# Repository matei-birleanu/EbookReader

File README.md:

# 📘 System Overview

This project brings together multiple hardware components to form a compact, smart, and efficient embedded system. It supports wireless communication, environmental monitoring, timekeeping, data storage, battery management, and user interaction via a low-power display.

---
## Schema Bloc

## 🔧 Components

### 🔲 **ESP32-C6-WROOM-1-N8**
- Acts as the main controller managing all tasks and data flow.
- Supports multiple wireless protocols: Wi-Fi, Bluetooth, Zigbee, and Thread.

### ⏱️ **RTC Module - DS3231SN**
- Ensures precise timekeeping.
- Communicates with the microcontroller via the I2C bus.

### 💾 **Flash Memory - W25Q512JVEIQ**
- High-speed storage accessed through the SPI interface.
- Used for firmware storage and persistent data.

### 🔋 **Battery Charging IC - MCP73831**
- Manages the charging process of a Li-Ion battery through the USB Type-C port.
- GPIO pins are used to monitor charging status and control power logic.

### ⚡ **Fuel Gauge - MAX17048G+T10**
- Estimates the battery's state of charge.
- Interfaces with the microcontroller over I2C.

### 🌡️ **Environmental Sensor - BME680**
- Measures temperature, humidity, atmospheric pressure, and gas levels.
- I2C-based communication.

### 🖼️ **ePaper Display**
- Displays system information to the user.
- Controlled via the SPI protocol for fast and efficient updates.

### 💽 **SD Card Slot (J4)**
- Enables external storage expansion.
- Useful for data logging or firmware upgrades.
- Communicates using the SPI interface.

### 🔌 **USB Type-C Port (J2)**
- Primary power supply for the device.
- Includes USB data lines (D+ and D−) for host communication.

---

## 📍 ESP32-C6 Pin Mapping

| ESP32-C6 Pin | Description |
|--------------|-------------|
| 3V3          | 3.3V output to power the charging circuit |
| EN           | Reset button |
| IO0          | Alert/timing signal from RTC |
| IO1          | Clock reference from RTC |
| IO2          | SPI - MISO (Master In Slave Out) |
| IO3          | ePaper display busy status |
| IO4          | SD card communication |
| IO5          | ePaper D/C (Data/Command select) |
| IO6          | SPI Clock (SCK) |
| IO7          | SPI - MOSI (Master Out Slave In) |
| IO8          | (Reserved/Unused) |
| IO9          | Boot button |
| IO10         | Chip Select for ePaper |
| IO11         | Chip Select for Flash memory |
| IO12         | USB D+ |
| IO13         | USB D− |
| IO15         | Mode switch button |
| TXD0 (IO16)  | UART TX for debugging |
| RXD0 (IO17)  | UART RX for debugging |
| IO18         | RTC reset |
| IO19         | I2C power line |
| IO20         | Power supply for the display |
| IO21         | I2C SDA (data line) |
| IO22         | I2C SCL (clock line) |
| IO23         | Display reset |
| GND          | Ground |

---

## BOM (Bill of Materials)

**Note**: TP-urile au fost construite de mine.

| Nr. piesa | Nume piesa       | Site                                                                                                                                           | Datasheet                                                                                                                                                    |
|-----------|------------------|------------------------------------------------------------------------------------------------------------------------------------------------|--------------------------------------------------------------------------------------------------------------------------------------------------------------|
| 1         | BOOT_BUTON       | [Link](https://www.snapeda.com/parts/EVQP7L01P/Panasonic%20Electronic%20Components/view-part/?welcome=home)                                   | [Datasheet](https://www.snapeda.com/parts/EVQP7L01P/Panasonic/datasheet/)                                                                                   |
| 2         | C1               | [Link](https://componentsearchengine.com/part-view/CC0402MRX5R5BB106/YAGEO)                                                                    | [Datasheet](https://componentsearchengine.com/Datasheets/2/CC0402MRX5R5BB106.pdf)                                                                           |
| 3         | C1_BAT           | [Link](https://componentsearchengine.com/part-view/CC0402MRX5R5BB106/YAGEO)                                                                    | [Datasheet](https://componentsearchengine.com/Datasheets/2/CC0402MRX5R5BB106.pdf)                                                                           |
| 4         | C1_BAT2          | [Link](https://componentsearchengine.com/part-view/CC0402MRX5R5BB106/YAGEO)                                                                    | [Datasheet](https://componentsearchengine.com/Datasheets/2/CC0402MRX5R5BB106.pdf)                                                                           |
| 5         | C2               | [Link](https://componentsearchengine.com/part-view/CC0402MRX5R5BB106/YAGEO)                                                                    | [Datasheet](https://componentsearchengine.com/Datasheets/2/CC0402MRX5R5BB106.pdf)                                                                           |
| 6         | C2_BAT           | [Link](https://componentsearchengine.com/part-view/CC0402MRX5R5BB106/YAGEO)                                                                    | [Datasheet](https://componentsearchengine.com/Datasheets/2/CC0402MRX5R5BB106.pdf)                                                                           |
| 7         | C3               | [Link](https://componentsearchengine.com/part-view/CC0402MRX5R5BB106/YAGEO)                                                                    | [Datasheet](https://componentsearchengine.com/Datasheets/2/CC0402MRX5R5BB106.pdf)                                                                           |
| 8         | C4               | [Link](https://componentsearchengine.com/part-view/CC0402MRX5R5BB106/YAGEO)                                                                    | [Datasheet](https://componentsearchengine.com/Datasheets/2/CC0402MRX5R5BB106.pdf)                                                                           |
| 9         | C4_USB           | [Link](https://componentsearchengine.com/part-view/CC0402MRX5R5BB106/YAGEO)                                                                    | [Datasheet](https://componentsearchengine.com/Datasheets/2/CC0402MRX5R5BB106.pdf)                                                                           |
| 10        | C5               | [Link](https://componentsearchengine.com/part-view/CC0402MRX5R5BB106/YAGEO)                                                                    | [Datasheet](https://componentsearchengine.com/Datasheets/2/CC0402MRX5R5BB106.pdf)                                                                           |
| 11        | C5_USB           | [Link](https://componentsearchengine.com/part-view/CC0402MRX5R5BB106/YAGEO)                                                                    | [Datasheet](https://componentsearchengine.com/Datasheets/2/CC0402MRX5R5BB106.pdf)                                                                           |
| 12        | C6               | [Link](https://componentsearchengine.com/part-view/CC0402MRX5R5BB106/YAGEO)                                                                    | [Datasheet](https://componentsearchengine.com/Datasheets/2/CC0402MRX5R5BB106.pdf)                                                                           |
| 13        | C7               | [Link](https://componentsearchengine.com/part-view/CC0402MRX5R5BB106/YAGEO)                                                                    | [Datasheet](https://componentsearchengine.com/Datasheets/2/CC0402MRX5R5BB106.pdf)                                                                           |
| 14        | C8               | [Link](https://componentsearchengine.com/part-view/CC0402MRX5R5BB106/YAGEO)                                                                    | [Datasheet](https://componentsearchengine.com/Datasheets/2/CC0402MRX5R5BB106.pdf)                                                                           |
| 15        | C9               | [Link](https://componentsearchengine.com/part-view/CC0402MRX5R5BB106/YAGEO)                                                                    | [Datasheet](https://componentsearchengine.com/Datasheets/2/CC0402MRX5R5BB106.pdf)                                                                           |
| 16        | C10              | [Link](https://componentsearchengine.com/part-view/CC0402MRX5R5BB106/YAGEO)                                                                    | [Datasheet](https://componentsearchengine.com/Datasheets/2/CC0402MRX5R5BB106.pdf)                                                                           |
| 17        | C10_SUPERCAR     | [Link](https://industry.panasonic.com/global/en/products/control/switch/light-touch/number/evqpuj02k)                                          | [Datasheet](https://industry.panasonic.com/global/en/downloads?tab=catalog&small_g_cd=203&part_no=EVQPUJ02K)                                                |
| 18        | CHANGE_BUTTON    | [Link](https://www.snapeda.com/parts/EVQP7L01P/Panasonic%20Electronic%20Components/view-part/?welcome=home)                                   | [Datasheet](https://www.snapeda.com/parts/EVQP7L01P/Panasonic/datasheet/)                                                                                   |
| 19        | C_DELAY          | [Link](https://componentsearchengine.com/part-view/CC0402MRX5R5BB106/YAGEO)                                                                    | [Datasheet](https://componentsearchengine.com/Datasheets/2/CC0402MRX5R5BB106.pdf)                                                                           |
| 20        | D1               | [Link](https://www.snapeda.com/parts/USBLC6-2SC6Y/STMicroelectronics/view-part/?ref=eda)                                                      | [Datasheet](https://www.snapeda.com/parts/USBLC6-2SC6Y/STMicroelectronics/view-part/?ref=eda)                                                               |
| 21        | D2               | [Link](https://ro.mouser.com/ProductDetail/KYOCERA-AVX/SD0805S020S1R0?qs=jCA%252BPfw4LHbpkAoSnwrdjw%3D%3D)                                      | [Datasheet](https://ro.mouser.com/datasheet/2/40/schottky-3165252.pdf)                                                                                      |
| 22        | D3               | [Link](https://ro.mouser.com/ProductDetail/KYOCERA-AVX/SD0805S020S1R0?qs=jCA%252BPfw4LHbpkAoSnwrdjw%3D%3D)                                      | [Datasheet](https://ro.mouser.com/datasheet/2/40/schottky-3165252.pdf)                                                                                      |
| 23        | D4               | [Link](https://ro.mouser.com/ProductDetail/KYOCERA-AVX/SD0805S020S1R0?qs=jCA%252BPfw4LHbpkAoSnwrdjw%3D%3D)                                      | [Datasheet](https://ro.mouser.com/datasheet/2/40/schottky-3165252.pdf)                                                                                      |
| 24        | D5               | [Link](https://ro.mouser.com/ProductDetail/KYOCERA-AVX/SD0805S020S1R0?qs=jCA%252BPfw4LHbpkAoSnwrdjw%3D%3D)                                      | [Datasheet](https://ro.mouser.com/datasheet/2/40/schottky-3165252.pdf)                                                                                      |
| 25        | D6               | [Link](https://www.snapeda.com/parts/PGB1010603MR/Littelfuse/view-part/?ref=eda)                                                              | [Datasheet](https://www.snapeda.com/parts/PGB1010603MR/Littelfuse%20Inc./datasheet/)                                                                        |
| 26        | D7               | [Link](https://ro.mouser.com/ProductDetail/KYOCERA-AVX/SD0805S020S1R0?qs=jCA%252BPfw4LHbpkAoSnwrdjw%3D%3D)                                      | [Datasheet](https://ro.mouser.com/datasheet/2/40/schottky-3165252.pdf)                                                                                      |
| 27        | D8               | [Link](https://www.snapeda.com/parts/PGB1010603MR/Littelfuse/view-part/?ref=eda)                                                              | [Datasheet](https://www.snapeda.com/parts/PGB1010603MR/Littelfuse%20Inc./datasheet/)                                                                        |
| 28        | D9               | [Link](https://www.snapeda.com/parts/PGB1010603MR/Littelfuse/view-part/?ref=eda)                                                              | [Datasheet](https://www.snapeda.com/parts/PGB1010603MR/Littelfuse%20Inc./datasheet/)                                                                        |
| 29        | D10              | [Link](https://www.snapeda.com/parts/PGB1010603MR/Littelfuse/view-part/?ref=eda)                                                              | [Datasheet](https://www.snapeda.com/parts/PGB1010603MR/Littelfuse%20Inc./datasheet/)                                                                        |
| 30        | D11              | [Link](https://www.snapeda.com/parts/PGB1010603MR/Littelfuse/view-part/?ref=eda)                                                              | [Datasheet](https://www.snapeda.com/parts/PGB1010603MR/Littelfuse%20Inc./datasheet/)                                                                        |
| 31        | D12              | [Link](https://www.snapeda.com/parts/PGB1010603MR/Littelfuse/view-part/?ref=eda)                                                              | [Datasheet](https://www.snapeda.com/parts/PGB1010603MR/Littelfuse%20Inc./datasheet/)                                                                        |
| 32        | EPD_C1           | [Link](https://componentsearchengine.com/part-view/CC0402MRX5R5BB106/YAGEO)                                                                    | [Datasheet](https://componentsearchengine.com/Datasheets/2/CC0402MRX5R5BB106.pdf)                                                                           |
| 33        | EPD_C2           | [Link](https://componentsearchengine.com/part-view/CC0402MRX5R5BB106/YAGEO)                                                                    | [Datasheet](https://componentsearchengine.com/Datasheets/2/CC0402MRX5R5BB106.pdf)                                                                           |
| 34        | EPD_C5           | [Link](https://componentsearchengine.com/part-view/CC0402MRX5R5BB106/YAGEO)                                                                    | [Datasheet](https://componentsearchengine.com/Datasheets/2/CC0402MRX5R5BB106.pdf)                                                                           |
| 35        | EPD_C6           | [Link](https://componentsearchengine.com/part-view/CC0402MRX5R5BB106/YAGEO)                                                                    | [Datasheet](https://componentsearchengine.com/Datasheets/2/CC0402MRX5R5BB106.pdf)                                                                           |
| 36        | EPD_C7           | [Link](https://componentsearchengine.com/part-view/CC0402MRX5R5BB106/YAGEO)                                                                    | [Datasheet](https://componentsearchengine.com/Datasheets/2/CC0402MRX5R5BB106.pdf)                                                                           |
| 37        | EPD_C8           | [Link](https://componentsearchengine.com/part-view/CC0402MRX5R5BB106/YAGEO)                                                                    | [Datasheet](https://componentsearchengine.com/Datasheets/2/CC0402MRX5R5BB106.pdf)                                                                           |
| 38        | EPD_C9           | [Link](https://componentsearchengine.com/part-view/CC0402MRX5R5BB106/YAGEO)                                                                    | [Datasheet](https://componentsearchengine.com/Datasheets/2/CC0402MRX5R5BB106.pdf)                                                                           |
| 39        | EPD_C10          | [Link](https://componentsearchengine.com/part-view/CC0402MRX5R5BB106/YAGEO)                                                                    | [Datasheet](https://componentsearchengine.com/Datasheets/2/CC0402MRX5R5BB106.pdf)                                                                           |
| 40        | EPD_C11          | [Link](https://componentsearchengine.com/part-view/CC0402MRX5R5BB106/YAGEO)                                                                    | [Datasheet](https://componentsearchengine.com/Datasheets/2/CC0402MRX5R5BB106.pdf)                                                                           |
| 41        | EPD_C12          | [Link](https://componentsearchengine.com/part-view/CC0402MRX5R5BB106/YAGEO)                                                                    | [Datasheet](https://componentsearchengine.com/Datasheets/2/CC0402MRX5R5BB106.pdf)                                                                           |
| 42        | IC1              | [Link](https://componentsearchengine.com/part-view/BD5229G-TR/ROHM%20Semiconductor)                                                            | [Datasheet](https://datasheet.datasheetarchive.com/originals/distributors/Datasheets_SAMA/f2b9741ef86007909f138d561a359946.pdf)                             |
| 43        | IC4              | [Link](https://componentsearchengine.com/part-view/XC6220A331MR-G/Torex)                                                                       | [Datasheet](https://product.torexsemi.com/system/files/series/xc6220.pdf)                                                                                   |
| 44        | J1               | [Link](https://componentsearchengine.com/part-view/FH34SRJ-24S-0.5SH%2899%29/Hirose)                                                           | [Datasheet](https://www.hirose.com/en/product/document?clcode=CL0580-1255-6-99&productname=FH34SRJ-24S-0.5SH%2899%29&series=FH34SRJ&documenttype=2DDrawing&lang=en&documentid=0000990903) |
| 45        | J2               | [Link](https://componentsearchengine.com/part-view/USB4110-GF-A/GCT%20(GLOBAL%20CONNECTOR%20TECHNOLOGY))                                       | [Datasheet](https://gct.co/files/drawings/usb4110.pdf)                                                                                                      |
| 46        | J3               | [Link](https://www.snapeda.com/parts/PRT-14417/SparkFun/view-part/)                                                                            | [Datasheet](https://www.snapeda.com/parts/PRT-14417/SparkFun%20Electronics/datasheet/)                                                                       |
| 47        | J4               | [Link](https://www.snapeda.com/parts/112A-TAAR-R03/Attend/view-part/)                                                                          | [Datasheet](https://www.snapeda.com/parts/112A-TAAR-R03/Attend/datasheet/)                                                                                  |
| 48        | MCP73831         | [Link](https://ro.mouser.com/ProductDetail/Microchip-Technology/MCP73831T-2ACI-OT?qs=yUQqVecv4qvbBQBGbHx0Mw%3D%3D&utm_id=20109199409&utm_source=google&utm_medium=cpc&utm_marketing_tactic=emeacorp&gad_source=1&gbraid=0AAAAADn_wf0-USzm1eg1ywGvQg_qMgG3H) | [Datasheet](https://ro.mouser.com/datasheet/2/268/MCP73831_Family_Data_Sheet_DS20001984H-3441711.pdf)                                                       |
| 49        | L1               | [Link](https://ro.mouser.com/ProductDetail/Wurth-Elektronik/744043680?qs=PGXP4M47uW6VkZq%252BkzjrHA%3D%3D)                                       | [Datasheet](https://www.we-online.com/components/products/datasheet/744043680.pdf)                                                                          |
| 50        | PFMF.050.1       | [Link](https://ro.mouser.com/ProductDetail/EPCOS-TDK/B72520T0350K062?qs=dEfas%2FXlABIszF52uu7vrg%3D%3D)                                         | [Datasheet](https://www.tdk-electronics.tdk.com/inf/75/db/CTVS_14/Surge_protection_series.pdf)                                                              |
| 51        | Q1               | [Link](https://componentsearchengine.com/part-view/DMG2305UX-7/Diodes%20Incorporated)                                                          | [Datasheet](https://www.diodes.com//assets/Datasheets/DMG2305UX.pdf)                                                                                        |
| 52        | Q2               | [Link](https://componentsearchengine.com/part-view/DMG2305UX-7/Diodes%20Incorporated)                                                          | [Datasheet](https://www.diodes.com//assets/Datasheets/DMG2305UX.pdf)                                                                                        |
| 53        | Q3               | [Link](https://componentsearchengine.com/part-view/SI1308EDL-T1-GE3/Vishay)                                                                     | [Datasheet](https://componentsearchengine.com/part-view/SI1308EDL-T1-GE3/Vishay)                                                                             |
| 54        | R1               | [Link](https://componentsearchengine.com/part-view/R0402%201%25%20100%20K%20%28RC0402FR-07100KL%29/YAGEO)                                       | [Datasheet](https://www.yageo.com/upload/media/product/products/datasheet/rchip/PYu-RC_Group_51_RoHS_L_12.pdf)                                              |
| 55        | R1_PINH          | [Link](https://componentsearchengine.com/part-view/R0402%201%25%20100%20K%20%28RC0402FR-07100KL%29/YAGEO)                                       | [Datasheet](https://www.yageo.com/upload/media/product/products/datasheet/rchip/PYu-RC_Group_51_RoHS_L_12.pdf)                                              |
| 56        | R1_PINH1         | [Link](https://componentsearchengine.com/part-view/R0402%201%25%20100%20K%20%28RC0402FR-07100KL%29/YAGEO)                                       | [Datasheet](https://www.yageo.com/upload/media/product/products/datasheet/rchip/PYu-RC_Group_51_RoHS_L_12.pdf)                                              |
| 57        | R1_BAT           | [Link](https://componentsearchengine.com/part-view/R0402%201%25%20100%20K%20%28RC0402FR-07100KL%29/YAGEO)                                       | [Datasheet](https://www.yageo.com/upload/media/product/products/datasheet/rchip/PYu-RC_Group_51_RoHS_L_12.pdf)                                              |
| 58        | R1_PWRUSB        | [Link](https://componentsearchengine.com/part-view/R0402%201%25%20100%20K%20%28RC0402FR-07100KL%29/YAGEO)                                       | [Datasheet](https://www.yageo.com/upload/media/product/products/datasheet/rchip/PYu-RC_Group_51_RoHS_L_12.pdf)                                              |
| 59        | R2               | [Link](https://componentsearchengine.com/part-view/R0402%201%25%20100%20K%20%28RC0402FR-07100KL%29/YAGEO)                                       | [Datasheet](https://www.yageo.com/upload/media/product/products/datasheet/rchip/PYu-RC_Group_51_RoHS_L_12.pdf)                                              |
| 60        | R2_PINH          | [Link](https://componentsearchengine.com/part-view/R0402%201%25%20100%20K%20%28RC0402FR-07100KL%29/YAGEO)                                       | [Datasheet](https://www.yageo.com/upload/media/product/products/datasheet/rchip/PYu-RC_Group_51_RoHS_L_12.pdf)                                              |
| 61        | R2-PINH1         | [Link](https://componentsearchengine.com/part-view/R0402%201%25%20100%20K%20%28RC0402FR-07100KL%29/YAGEO)                                       | [Datasheet](https://www.yageo.com/upload/media/product/products/datasheet/rchip/PYu-RC_Group_51_RoHS_L_12.pdf)                                              |
| 62        | R2               | [Link](https://componentsearchengine.com/part-view/R0402%201%25%20100%20K%20%28RC0402FR-07100KL%29/YAGEO)                                       | [Datasheet](https://www.yageo.com/upload/media/product/products/datasheet/rchip/PYu-RC_Group_51_RoHS_L_12.pdf)                                              |
| 63        | R2-PINH          | [Link](https://componentsearchengine.com/part-view/R0402%201%25%20100%20K%20%28RC0402FR-07100KL%29/YAGEO)                                       | [Datasheet](https://www.yageo.com/upload/media/product/products/datasheet/rchip/PYu-RC_Group_51_RoHS_L_12.pdf)                                              |
| 64        | R2-PINH1         | [Link](https://componentsearchengine.com/part-view/R0402%201%25%20100%20K%20%28RC0402FR-07100KL%29/YAGEO)                                       | [Datasheet](https://www.yageo.com/upload/media/product/products/datasheet/rchip/PYu-RC_Group_51_RoHS_L_12.pdf)                                              |
| 65        | R2_USB           | [Link](https://componentsearchengine.com/part-view/R0402%201%25%20100%20K%20%28RC0402FR-07100KL%29/YAGEO)                                       | [Datasheet](https://www.yageo.com/upload/media/product/products/datasheet/rchip/PYu-RC_Group_51_RoHS_L_12.pdf)                                              |
| 66        | R2_USB           | [Link](https://componentsearchengine.com/part-view/R0402%201%25%20100%20K%20%28RC0402FR-07100KL%29/YAGEO)                                       | [Datasheet](https://www.yageo.com/upload/media/product/products/datasheet/rchip/PYu-RC_Group_51_RoHS_L_12.pdf)                                              |
| 67        | R2_USB1          | [Link](https://componentsearchengine.com/part-view/R0402%201%25%20100%20K%20%28RC0402FR-07100KL%29/YAGEO)                                       | [Datasheet](https://www.yageo.com/upload/media/product/products/datasheet/rchip/PYu-RC_Group_51_RoHS_L_12.pdf)                                              |
| 68        | R3               | [Link](https://componentsearchengine.com/part-view/R0402%201%25%20100%20K%20%28RC0402FR-07100KL%29/YAGEO)                                       | [Datasheet](https://www.yageo.com/upload/media/product/products/datasheet/rchip/PYu-RC_Group_51_RoHS_L_12.pdf)                                              |
| 69        | R4               | [Link](https://componentsearchengine.com/part-view/R0402%201%25%20100%20K%20%28RC0402FR-07100KL%29/YAGEO)                                       | [Datasheet](https://www.yageo.com/upload/media/product/products/datasheet/rchip/PYu-RC_Group_51_RoHS_L_12.pdf)                                              |
| 70        | R5               | [Link](https://componentsearchengine.com/part-view/R0402%201%25%20100%20K%20%28RC0402FR-07100KL%29/YAGEO)                                       | [Datasheet](https://www.yageo.com/upload/media/product/products/datasheet/rchip/PYu-RC_Group_51_RoHS_L_12.pdf)                                              |
| 71        | R6               | [Link](https://componentsearchengine.com/part-view/R0402%201%25%20100%20K%20%28RC0402FR-07100KL%29/YAGEO)                                       | [Datasheet](https://www.yageo.com/upload/media/product/products/datasheet/rchip/PYu-RC_Group_51_RoHS_L_12.pdf)                                              |
| 72        | R7               | [Link](https://componentsearchengine.com/part-view/R0402%201%25%20100%20K%20%28RC0402FR-07100KL%29/YAGEO)                                       | [Datasheet](https://www.yageo.com/upload/media/product/products/datasheet/rchip/PYu-RC_Group_51_RoHS_L_12.pdf)                                              |
| 73        | R8               | [Link](https://componentsearchengine.com/part-view/R0402%201%25%20100%20K%20%28RC0402FR-07100KL%29/YAGEO)                                       | [Datasheet](https://www.yageo.com/upload/media/product/products/datasheet/rchip/PYu-RC_Group_51_RoHS_L_12.pdf)                                              |
| 74        | R9               | [Link](https://componentsearchengine.com/part-view/R0402%201%25%20100%20K%20%28RC0402FR-07100KL%29/YAGEO)                                       | [Datasheet](https://www.yageo.com/upload/media/product/products/datasheet/rchip/PYu-RC_Group_51_RoHS_L_12.pdf)                                              |
| 75        | R10              | [Link](https://componentsearchengine.com/part-view/R0402%201%25%20100%20K%20%28RC0402FR-07100KL%29/YAGEO)                                       | [Datasheet](https://www.yageo.com/upload/media/product/products/datasheet/rchip/PYu-RC_Group_51_RoHS_L_12.pdf)                                              |
| 76        | RESET_BUTTON     | [Link](https://www.snapeda.com/parts/EVQP7L01P/Panasonic%20Electronic%20Components/view-part/?welcome=home)                                   | [Datasheet](https://www.snapeda.com/parts/EVQP7L01P/Panasonic/datasheet/)                                                                                   |
| 77        | R_BOOT           | [Link](https://componentsearchengine.com/part-view/R0402%201%25%20100%20K%20%28RC0402FR-07100KL%29/YAGEO)                                       | [Datasheet](https://www.yageo.com/upload/media/product/products/datasheet/rchip/PYu-RC_Group_51_RoHS_L_12.pdf)                                              |
| 78        | R_CAPACITOR      | [Link](https://componentsearchengine.com/part-view/R0402%201%25%20100%20K%20%28RC0402FR-07100KL%29/YAGEO)                                       | [Datasheet](https://www.yageo.com/upload/media/product/products/datasheet/rchip/PYu-RC_Group_51_RoHS_L_12.pdf)                                              |
| 79        | R_CHANGE         | [Link](https://componentsearchengine.com/part-view/R0402%201%25%20100%20K%20%28RC0402FR-07100KL%29/YAGEO)                                       | [Datasheet](https://www.yageo.com/upload/media/product/products/datasheet/rchip/PYu-RC_Group_51_RoHS_L_12.pdf)                                              |
| 80        | R_CL1            | [Link](https://componentsearchengine.com/part-view/R0402%201%25%20100%20K%20%28RC0402FR-07100KL%29/YAGEO)                                       | [Datasheet](https://www.yageo.com/upload/media/product/products/datasheet/rchip/PYu-RC_Group_51_RoHS_L_12.pdf)                                              |
| 81        | R_RESET          | [Link](https://componentsearchengine.com/part-view/R0402%201%25%20100%20K%20%28RC0402FR-07100KL%29/YAGEO)                                       | [Datasheet](https://www.yageo.com/upload/media/product/products/datasheet/rchip/PYu-RC_Group_51_RoHS_L_12.pdf)                                              |
| 82        | SENSOR2          | [Link](https://www.snapeda.com/parts/BME680/Bosch/view-part/?welcome=home)                                                                    | [Datasheet](https://www.snapeda.com/parts/BME680/Bosch%20Sensortec/datasheet/)                                                                               |
| 83        | SJ1              | [Link](https://grabcad.com/library/solder-jumpers-1)                                                                                           | [Datasheet](https://grabcad.com/library/solder-jumpers-1)                                                                                                   |
| 84        | TP1              |                                                                                                                                                 |                                                                                                                                                              |
| 85        | TP2              |                                                                                                                                                 |                                                                                                                                                              |
| 86        | TP3              |                                                                                                                                                 |                                                                                                                                                              |
| 87        | TP4              |                                                                                                                                                 |                                                                                                                                                              |
| 88        | TP5              |                                                                                                                                                 |                                                                                                                                                              |
| 89        | TP6              |                                                                                                                                                 |                                                                                                                                                              |
| 90        | TP7              |                                                                                                                                                 |                                                                                                                                                              |
| 91        | TP8              |                                                                                                                                                 |                                                                                                                                                              |
| 92        | TP9              |                                                                                                                                                 |                                                                                                                                                              |
| 93        | TP10             |                                                                                                                                                 |                                                                                                                                                              |
| 94        | TP11             |                                                                                                                                                 |                                                                                                                                                              |
| 95        | TP12             |                                                                                                                                                 |                                                                                                                                                              |
| 96        | TP13             |                                                                                                                                                 |                                                                                                                                                              |
| 97        | TP14             |                                                                                                                                                 |                                                                                                                                                              |
| 98        | TP15             |                                                                                                                                                 |                                                                                                                                                              |
| 99        | TP16             |                                                                                                                                                 |                                                                                                                                                              |
| 100       | TP17             |                                                                                                                                                 |                                                                                                                                                              |
| 101       | U1               | [Link](https://www.snapeda.com/parts/W25Q512JVEIQ/Winbond+Electronics/view-part/?ref=eda)                                                     | [Datasheet](https://www.snapeda.com/parts/W25Q512JVEIQ/Winbond+Electronics/view-part/?ref=eda)                                                              |
| 102       | U2               | [Link](https://www.snapeda.com/parts/ESP32-C6-WROOM-1-N8/Espressif+Systems/view-part/?ref=eda)                                                | [Datasheet](https://www.snapeda.com/parts/ESP32-C6-WROOM-1-N8/Espressif%20Systems/datasheet/)                                                               |
| 103       | U3               | [Link](https://www.snapeda.com/parts/DS3231SN%23/Analog+Devices/view-part/?ref=eda)                                                           | [Datasheet](https://www.snapeda.com/parts/DS3231SN%23/Analog%20Devices/datasheet/)                                                                          |
| 104       | U4               | [Link](https://www.snapeda.com/parts/MAX17048G+T10/Analog+Devices/view-part/?ref=eda)                                                         | [Datasheet](https://www.snapeda.com/parts/MAX17048G+T10/Analog%20Devices/datasheet/)         
                                         |

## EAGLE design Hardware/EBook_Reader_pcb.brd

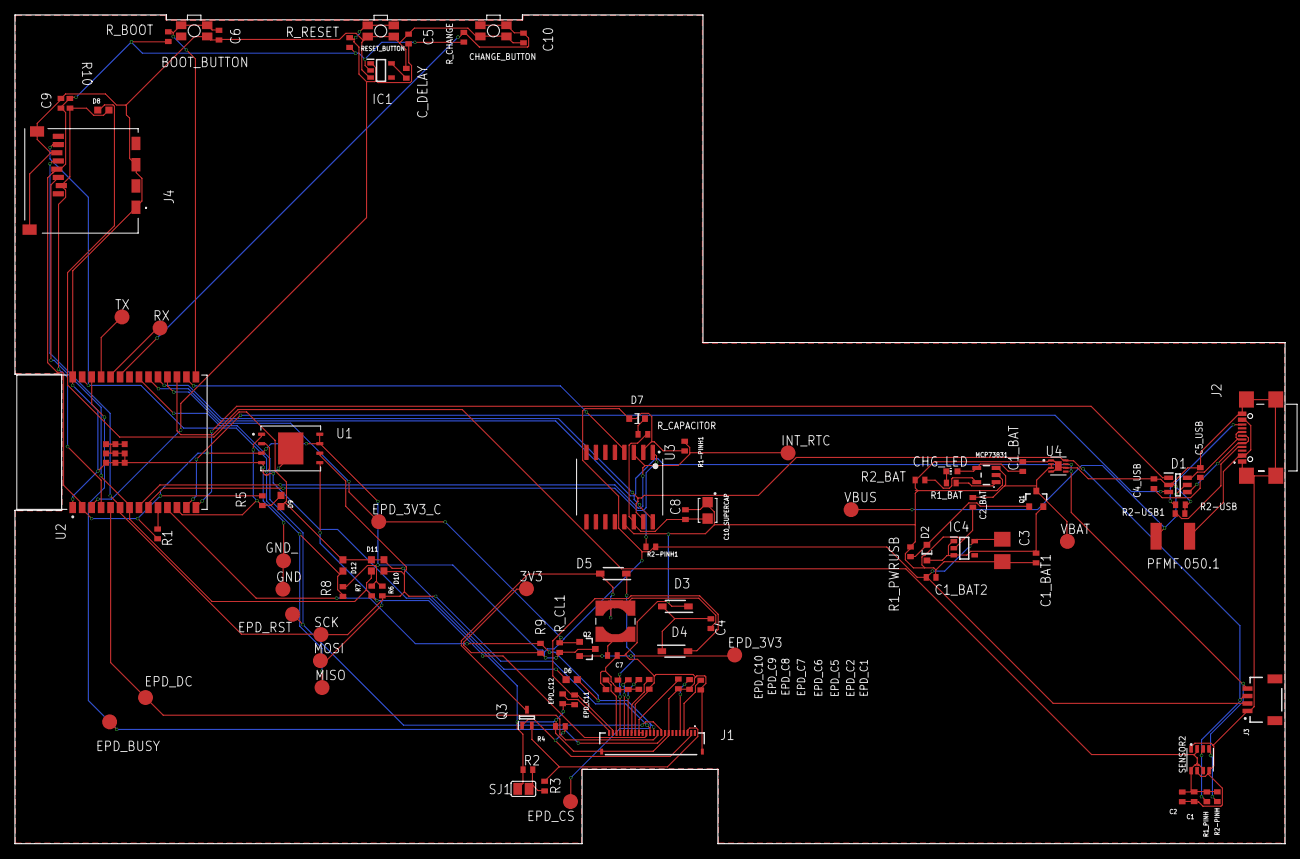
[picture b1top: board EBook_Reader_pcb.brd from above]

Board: 2 copper layers, 170.2 x 111.1 mm, 103 parts (0 on the bottom side), 61 nets.

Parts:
3V3: TPTP20R; TP20R
BOOT_BUTTON: BUTTON_CUSYOMV1; MYBUTTON
C1, C2, C4_USB, C6, C8, C9, C10: 100nF; ESP32_WROVER_EAGLE-LTSPICE_C0402
C1_BAT, C1_BAT1, C1_BAT2, C2_BAT, C5_USB: 4.7uF; ESP32_WROVER_EAGLE-LTSPICE_C0402
C3: 100uF TANT; RCL_CT3528
C4: 4.7uF/25V; ESP32_WROVER_EAGLE-LTSPICE_C0402
C5: 1uF; ESP32_WROVER_EAGLE-LTSPICE_C0402
C7: 10uF; ESP32_WROVER_EAGLE-LTSPICE_C0402
C10_SUPERCAP: CPH3225A; CAPCP3225X100N
CHANGE_BUTTON: BUTTON_CUSYOMV1; MYBUTTON
CHG_LED: ADAFRUIT_CHIP-LED0603
C_DELAY: 100nF; ESP32_WROVER_EAGLE-LTSPICE_C0402
D1: USBLC6-2SC6Y; SOT95P280X145-6N
D2, D7: ESP32_WROVER_AVX---SD0805S020S1R0_AVX_SD0805S020S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; ESP32_WROVER_AVX---SD0805S020S1R0_AVX_SD0805S020S1R0_0
D3, D4, D5: MBR0530; SOD3716X135N
D6, D8, D9, D10, D11, D12: PGB1010603MR; DIOC1608X36N
EPD_3V3, EPD_3V3_C: TPTP20R; TP20R
EPD_BUSY: TPTP20R; TP20R
EPD_C1, EPD_C2, EPD_C5, EPD_C6, EPD_C7, EPD_C8, EPD_C9, EPD_C10, EPD_C11, EPD_C12: 1uF/50V; ESP32_WROVER_EAGLE-LTSPICE_C0402
EPD_CS: TPTP20R; TP20R
EPD_DC: TPTP20R; TP20R
EPD_RST: TPTP20R; TP20R
GND: TPTP20R; TP20R
GND_: TPTP20R; TP20R
IC1: BD5229G-TR; SOT95P280X125-5N
IC4: XC6220A331MR-G; SOT95P280X120-5N
INT_RTC: TPTP20R; TP20R
J1: FH34SRJ-24S-0.5SH_99_; FH34SRJ24S05SH99
J2: SAMACSYS_PARTS_USB4110-GF-A; SAMACSYS_PARTS_USB4110GFA
J3: QWIIC_RIGHT_ANGLE; JST04_1MM_RA
J4: 112A-TAAR-R03_ATTEND; 112ATAARR03ATTEND
L1: 68uH; IND_4828-WE-TPC_WRE
MCP73831: ESP32_WROVER_SPARKFUN-IC-POWER_MCP73831; ESP32_WROVER_SPARKFUN-IC-POWER_SOT23-5
MISO: TPTP20R; TP20R
MOSI: TPTP20R; TP20R
PFMF.050.1: ESP32C6_VARISTORCN1812; ESP32C6_VARISTOR_CT/CN1812
Q1, Q2: 20V/4.2A/52mΩ/1.4W; ESP32_WROVER_SPARKFUN-DISCRETESEMI_SOT23-3
Q3: SI1308EDL-T1-GE3; SOT65P210X110-3N
R1, R1-PINH1, R1_PINH, R2-PINH, R2-PINH1, R4, R5, R6, R7, R8, R9, R10: 10K; ESP32_WROVER_EAGLE-LTSPICE_R0402
R1_BAT: 200; ESP32_WROVER_EAGLE-LTSPICE_R0402
R1_PWRUSB: 100K; ESP32_WROVER_EAGLE-LTSPICE_R0402
R2: 2.2; ESP32_WROVER_EAGLE-LTSPICE_R0402
R2-USB, R2-USB1: 5k1; ESP32_WROVER_EAGLE-LTSPICE_R0402
R2_BAT: 2K; ESP32_WROVER_EAGLE-LTSPICE_R0402
R3: 0.47; ESP32_WROVER_EAGLE-LTSPICE_R0402
RESET_BUTTON: BUTTON_CUSYOMV1; MYBUTTON
RX: TPTP20R; TP20R
R_BOOT: 10K; ESP32_WROVER_EAGLE-LTSPICE_R0402
R_CAPACITOR: 15; ESP32_WROVER_EAGLE-LTSPICE_R0402
R_CHANGE: 10K; ESP32_WROVER_EAGLE-LTSPICE_R0402
R_CL1: 10k; ESP32_WROVER_EAGLE-LTSPICE_R0402
R_RESET: 10k; ESP32_WROVER_EAGLE-LTSPICE_R0402
SCK: TPTP20R; TP20R
SENSOR2: ESP32_WROVER_BME680_BME680; ESP32_WROVER_BME680_PSON80P300X300X100-8N
SJ1: SJ
TX: TPTP20R; TP20R
U1: W25Q512JVEIQ; SON127P600X800X80-9N
U2: ESP32-C6-WROOM-1-N8; XCVR_ESP32-C6-WROOM-1-N8
U3: DS3231SN#; SOIC127P1032X265-16N
U4: MAX17048G+T10; SON50P200X200X80-9N
VBAT: TPTP20R; TP20R
VBUS: TPTP20R; TP20R

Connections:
3V3: 3V3.TP, C1_BAT2.1, C3.+, C9.1, D7.2, IC1.2, IC4.5, J3.2, J4.P4, Q2.3, R1.2, R1-PINH1.2, R2-PINH1.2, R5.2, R6.2, R7.2, R8.2, R9.2, R10.2, R_BOOT.1, R_CHANGE.1, R_CL1.2, R_RESET.1, U1.3, U1.7, U1.8, U2.2, U3.2
32KHZ: R2-PINH1.1, U2.9, U3.1
DN: D1.4, J2.A7, J2.B7
DP: D1.6, J2.A6, J2.B6
EPD_3V3: EPD_3V3.TP, Q2.2
EPD_3V3_C: EPD_3V3_C.TP, Q2.1, R_CL1.1, U2.18
EPD_BUSY: EPD_BUSY.TP, J1.9, U2.26
EPD_CS: D6.2, EPD_CS.TP, J1.12, R9.1, U2.11
EPD_DC: EPD_DC.TP, J1.11, U2.5
EPD_RST: EPD_RST.TP, J1.10, U2.21
FLASH_CS: D9.2, R5.1, U1.1, U2.12
GDR: J1.2, Q3.1, R4.2
GND: BOOT_BUTTON.2, C1.2, C1_BAT.2, C1_BAT1.2, C1_BAT2.2, C2.2, C2_BAT.2, C3.-, C4_USB.2, C5.2, C5_USB.2, C6.2, C7.2, C8.2, C9.2, C10.2, C10_SUPERCAP.1, CHANGE_BUTTON.1, CHANGE_BUTTON.2, C_DELAY.2, D1.2, D3.1, EPD_C1.2, EPD_C2.2, EPD_C5.2, EPD_C6.2, EPD_C7.2, EPD_C8.2, EPD_C9.2, EPD_C10.2, EPD_C11.2, EPD_C12.2, GND.TP, GND_.TP, IC1.3, IC4.2, J1.8, J1.17, J1.MP1, J1.MP2, J2.A1, J2.A12, J2.B1, J2.B12, J2.MP1, J2.MP2, J2.MP3, J2.MP4, J3.1, J4.G1, J4.G2, J4.G3, J4.G4, J4.P6, MCP73831.2, R1_PWRUSB.1, R2.1, R2-USB.2, R2-USB1.1, R2_BAT.1, R4.1, RESET_BUTTON.1, RESET_BUTTON.2, SENSOR2.1, SENSOR2.5, SENSOR2.7, SJ1.1, U1.4, U1.9, U2.1, U2.28, U2.29_1, U2.29_2, U2.29_3, U2.29_4, U2.29_5, U2.29_6, U2.29_7, U2.29_8, U2.29_9, U3.13, U4.1, U4.4, U4.6, U4.9
GND1: D6.1, D8.1, D9.1, D10.1, D11.1, D12.1
GPIO8: R1.1, U2.10
I2C_PW: C1.1, C2.1, R1_PINH.2, R2-PINH.2, SENSOR2.2, SENSOR2.6, SENSOR2.8, U2.17
INT_RTC: INT_RTC.TP, R1-PINH1.1, U2.8, U3.3
IO/BOOT: BOOT_BUTTON.3, BOOT_BUTTON.4, C6.1, R_BOOT.2, U2.15
IO/CHANGE: C10.1, CHANGE_BUTTON.3, CHANGE_BUTTON.4, R_CHANGE.2, U2.23
MISO: D12.2, J4.P7, MISO.TP, R8.1, U1.2, U2.27
MOSI: D11.2, J1.14, J4.P3, MOSI.TP, R7.1, U1.5, U2.7
unnamed: J2.B5, R2-USB.1
unnamed: EPD_C2.1, J1.5
unnamed: EPD_C1.1, J1.4
unnamed: J2.A5, R2-USB1.2
unnamed: C_DELAY.1, IC1.5
unnamed: D7.1, R_CAPACITOR.1
unnamed: C4_USB.1, C5_USB.1
unnamed: D2.2, Q1.1, R1_PWRUSB.2
unnamed: C1_BAT1.1, D2.1, IC4.1, IC4.3, Q1.2
unnamed: C7.1, L1.2
unnamed: C4.1, D3.2, D4.1
unnamed: C1_BAT.1, CHG_LED.A, MCP73831.4
unnamed: CHG_LED.C, R1_BAT.1
unnamed: MCP73831.1, R1_BAT.2
unnamed: MCP73831.5, R2_BAT.2
unnamed: EPD_C12.1, J1.24
unnamed: EPD_C10.1, J1.22
unnamed: EPD_C8.1, J1.20
unnamed: EPD_C7.1, J1.19
unnamed: EPD_C6.1, J1.18
unnamed: EPD_C5.1, J1.15, J1.16
PREVGH: D5.1, EPD_C9.1, J1.21
PREVGL: D4.2, EPD_C11.1, J1.23
RESE: J1.3, Q3.2, R3.2
RESE': R2.2, R3.1, SJ1.2
RESET: C5.1, IC1.1, RESET_BUTTON.3, RESET_BUTTON.4, R_RESET.2, U2.3
RTC_RST: U2.16, U3.4
RX: RX.TP, U2.24
SCK: D10.2, J1.13, J4.P5, R6.1, SCK.TP, U1.6, U2.6
SCL: J3.4, R2-PINH.1, SENSOR2.4, U2.20, U3.16, U4.7
SDA: J3.3, R1_PINH.1, SENSOR2.3, U2.19, U3.15, U4.8
SRC: C4.2, D5.2, L1.1, Q3.3
SS_SD: D8.2, J4.P2, R10.1, U2.4
TX: TX.TP, U2.25
USB_D+: D1.1, U2.14
USB_D-: D1.3, U2.13
VBAT: C2_BAT.1, MCP73831.3, Q1.3, U4.2, U4.3, VBAT.TP
VBUS: D1.5, PFMF.050.1.2, VBUS.TP
VRTC: C8.1, C10_SUPERCAP.2, R_CAPACITOR.2, U3.14
VUSB: J2.A4, J2.A9, J2.B4, J2.B9, PFMF.050.1.1

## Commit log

2025-04-06 Finalized projects
2025-04-06 Create LICENSE

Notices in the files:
parts and their libraries:
COPYRIGHT: Copyright (C) 2024 Ultra Librarian. All rights reserved.
